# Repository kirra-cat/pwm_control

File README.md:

# pwm_control
Система управления элементами Пельтье

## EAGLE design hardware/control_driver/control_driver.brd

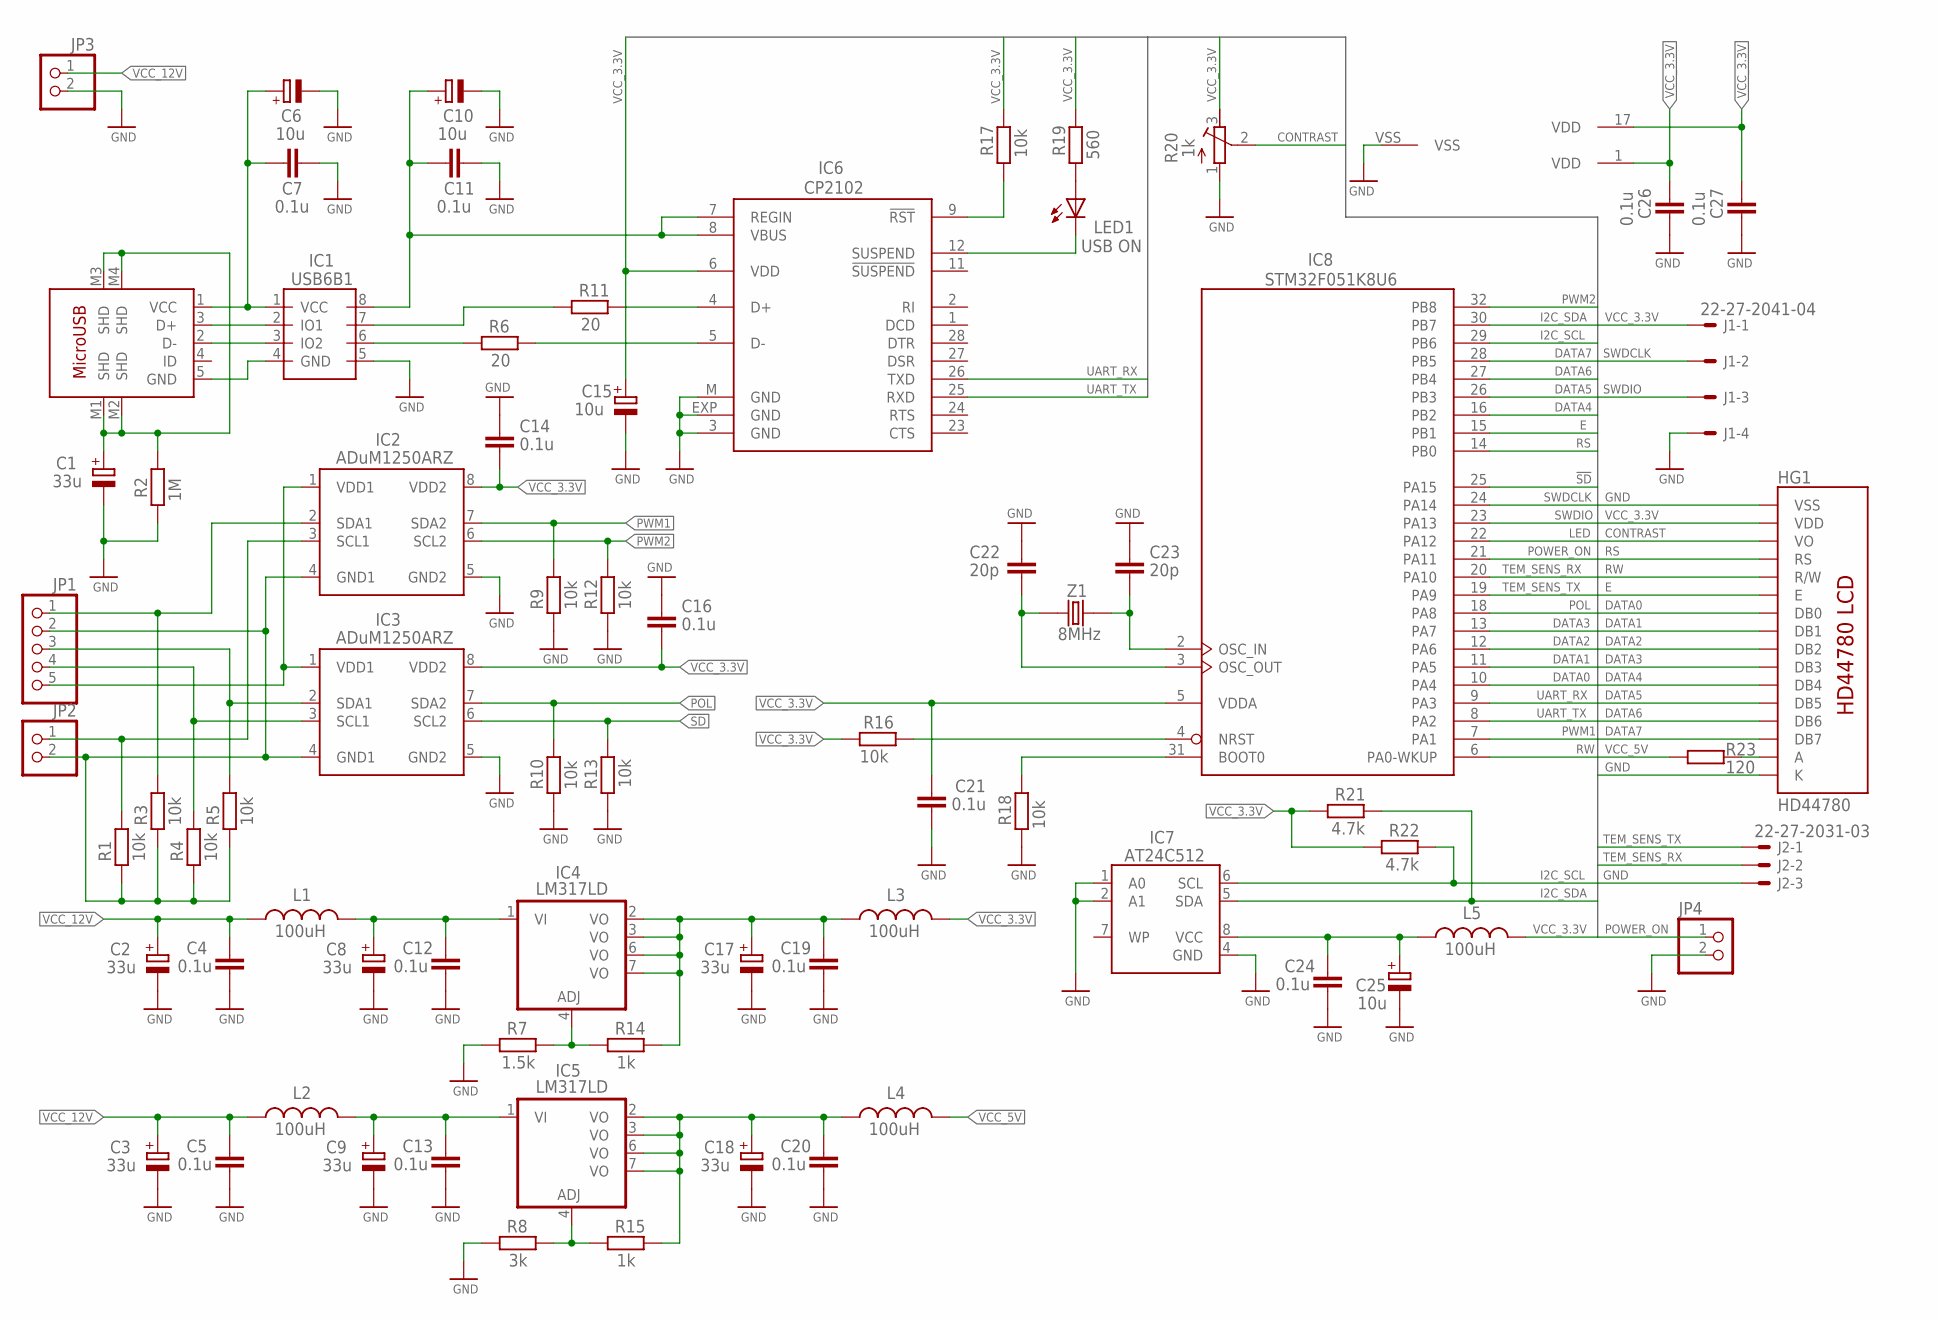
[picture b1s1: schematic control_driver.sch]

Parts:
C1, C17, C18: 33u; SMC_B
C2, C3, C8, C9: 33u; SMC_C
C4, C5, C7, C11, C12, C13, C14, C16, C19, C20, C21, C24, C26, C27: 0.1u; C0603
C6, C10, C15, C25: 10u; SMC_A
C22, C23: 20p; C0603
HG1: HD44780; LCD-16X2-4HOLES
IC1: USB6B1; SO08
IC2, IC3: ADuM1250ARZ; SO8
IC4, IC5: LM317LD; SO08
IC6: CP2102; MLP28
IC7: AT24C512; SO8
IC8: STM32F051K8U6; UFQFPN32
J1: 22-27-2041-04; 6410-04
J2: 22-27-2031-03; 6410-03
JP1: PINHD-1X55X2MM; 1_05X2MM
JP2, JP3, JP4: PINHD-1X2; 1X02
L1, L2, L3, L4, L5: 100uH; C0603
LED1: USB ON; CHIPLED_0805
R1, R3, R4, R5, R9, R10, R12, R13, R16, R17, R18: 10k; R0603
R2: 1M; R0603
R6, R11: 20; R0603
R7: 1.5k; R0603
R8: 3k; R0603
R14, R15: 1k; R0603
R19: 560; R0603
R20: 1k; RTRIM4G/J
R21, R22: 4.7k; R0603
R23: 120; R0805
X1: MICRO-USB; ZX62R-B-5P
Z1: 8MHz; CRYSTAL_5X7

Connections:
!SD: IC3.6 (SCL2), IC8.25 (PA15), R13.2
CONTRAST: HG1.3 (VO), R20.2 (S)
DATA0: HG1.7 (DB0), IC8.10 (PA4)
DATA1: HG1.8 (DB1), IC8.11 (PA5)
DATA2: HG1.9 (DB2), IC8.12 (PA6)
DATA3: HG1.10 (DB3), IC8.13 (PA7)
DATA4: HG1.11 (DB4), IC8.16 (PB2)
DATA5: HG1.12 (DB5), IC8.26 (PB3)
DATA6: HG1.13 (DB6), IC8.27 (PB4)
DATA7: HG1.14 (DB7), IC8.28 (PB5)
E: HG1.6 (E), IC8.15 (PB1)
GND: C1.-, C2.-, C3.-, C4.1, C5.1, C6.-, C7.2, C8.-, C9.-, C10.-, C11.2, C12.1, C13.1, C14.2, C15.-, C16.2, C17.-, C18.-, C19.1, C20.1, C21.1, C22.2, C23.2, C24.1, C25.-, C26.1, C27.1, HG1.1 (VSS), HG1.16 (K), IC1.5 (GND), IC2.5 (GND2), IC3.5 (GND2), IC6.3 (GND), IC6.EXP (GND), IC6.M (GND), IC7.1 (A0), IC7.2 (A1), IC7.4 (GND), IC8.VSS, J1.4, J2.3, JP3.2, JP4.2, R2.1, R7.1, R8.1, R9.1, R10.1, R12.1, R13.1, R18.1, R20.1 (A)
I2C_SCL: IC7.6 (SCL), IC8.29 (PB6), R22.2
I2C_SDA: IC7.5 (SDA), IC8.30 (PB7), R21.2
LED: IC8.22 (PA12)
unnamed: HG1.15 (A), R23.2
unnamed: IC1.6 (IO2), R6.1
unnamed: IC1.7 (IO1), R11.1
unnamed: IC6.5 (D-), R6.2
unnamed: IC6.4 (D+), R11.2
unnamed: LED1.A, R19.1
unnamed: C10.+, C11.1, IC1.8 (VCC), IC6.7 (REGIN), IC6.8 (VBUS)
unnamed: IC6.9 (!RST), R17.1
unnamed: IC6.12 (SUSPEND), LED1.C
unnamed: IC4.4 (ADJ), R7.2, R14.1
unnamed: C8.+, C12.2, IC4.1 (VI), L1.2
unnamed: IC5.4 (ADJ), R8.2, R15.1
unnamed: C1.+, R2.2, X1.M1 (SHD), X1.M2 (SHD), X1.M3 (SHD), X1.M4 (SHD)
unnamed: IC1.2 (IO1), X1.3 (D+)
unnamed: IC1.3 (IO2), X1.2 (D-)
unnamed: IC1.4 (GND), X1.5 (GND)
unnamed: C6.+, C7.1, IC1.1 (VCC), X1.1 (VCC)
unnamed: C22.1, IC8.3 (OSC_OUT), Z1.P$1 (1)
unnamed: C23.1, IC8.2 (OSC_IN), Z1.P$2 (2)
unnamed: C24.2, C25.+, IC7.8 (VCC), L5.1
unnamed: IC8.4 (NRST), R16.2
unnamed: IC2.1 (VDD1), IC3.1 (VDD1), JP1.5
unnamed: IC8.31 (BOOT0), R18.2
unnamed: IC2.3 (SCL1), JP2.1, R1.2
unnamed: IC2.2 (SDA1), JP1.1, R3.2
unnamed: IC3.2 (SDA1), JP1.3, R5.2
unnamed: IC3.3 (SCL1), JP1.4, R4.2
unnamed: IC2.4 (GND1), IC3.4 (GND1), JP1.2, JP2.2, R1.1, R3.1, R4.1, R5.1
POL: IC3.7 (SDA2), IC8.18 (PA8), R10.2
POWER_ON: IC8.21 (PA11), JP4.1
PWM1: IC2.7 (SDA2), IC8.7 (PA1), R9.2
PWM2: IC2.6 (SCL2), IC8.32 (PB8), R12.2
RS: HG1.4 (RS), IC8.14 (PB0)
RW: HG1.5 (R/W), IC8.6 (PA0-WKUP)
SWDCLK: IC8.24 (PA14), J1.2
SWDIO: IC8.23 (PA13), J1.3
TEM_SENS_RX: IC8.20 (PA10), J2.2
TEM_SENS_TX: IC8.19 (PA9), J2.1
UART_RX: IC6.26 (TXD), IC8.9 (PA3)
UART_TX: IC6.25 (RXD), IC8.8 (PA2)
VCC_3.3V: C14.1, C15.+, C16.1, C21.2, C26.2, C27.2, HG1.2 (VDD), IC2.8 (VDD2), IC3.8 (VDD2), IC6.6 (VDD), IC8.1 (VDD), IC8.5 (VDDA), IC8.17 (VDD), J1.1, L3.2, L5.2, R16.1, R17.2, R19.2, R20.3 (E), R21.1, R22.1
VCC_3.3V1: C18.+, C20.2, IC5.2 (VO), IC5.3 (VO), IC5.6 (VO), IC5.7 (VO), L4.1, R15.2
VCC_3.3V2222: C17.+, C19.2, IC4.2 (VO), IC4.3 (VO), IC4.6 (VO), IC4.7 (VO), L3.1, R14.2
VCC_5V: L4.2, R23.1
VCC_12V: C2.+, C3.+, C4.2, C5.2, JP3.1, L1.1, L2.1
VCC_12V_IN: C9.+, C13.2, IC5.1 (VI), L2.2

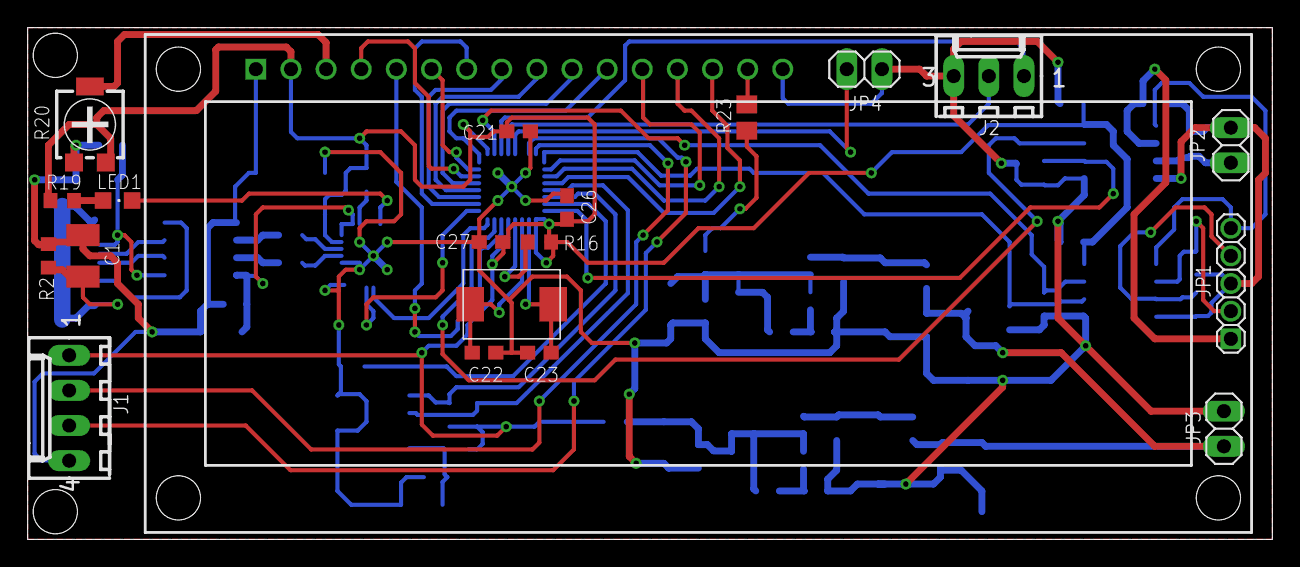
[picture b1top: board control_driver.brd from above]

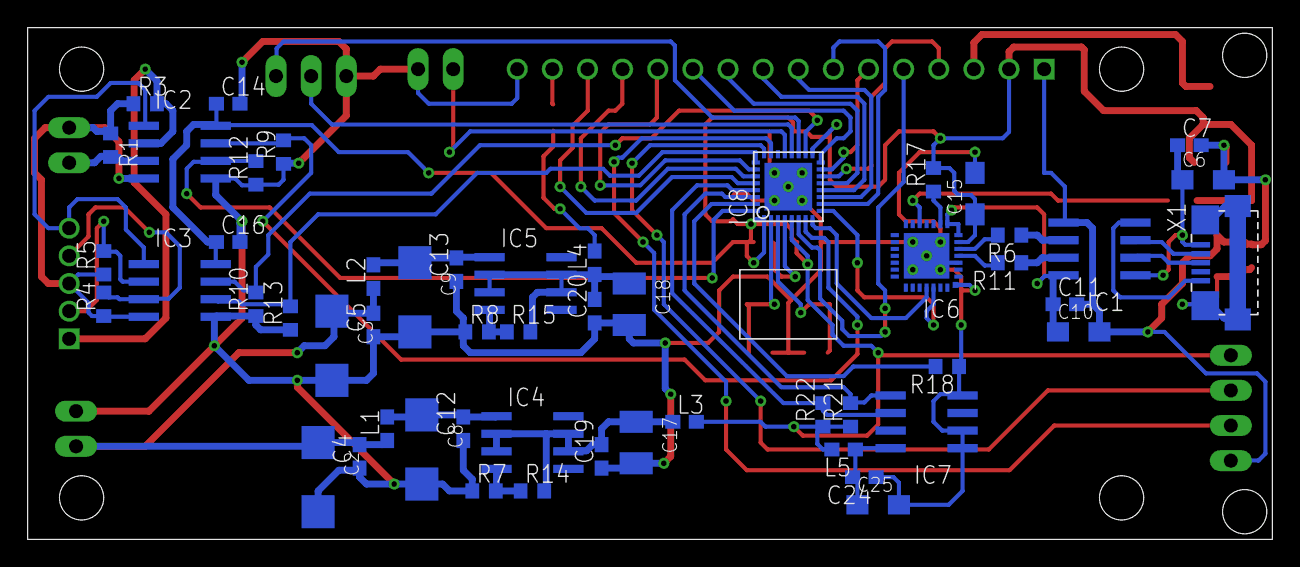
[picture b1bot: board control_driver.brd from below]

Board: 2 copper layers, 89.9 x 36.9 mm, 73 parts (53 on the bottom side), 60 nets.

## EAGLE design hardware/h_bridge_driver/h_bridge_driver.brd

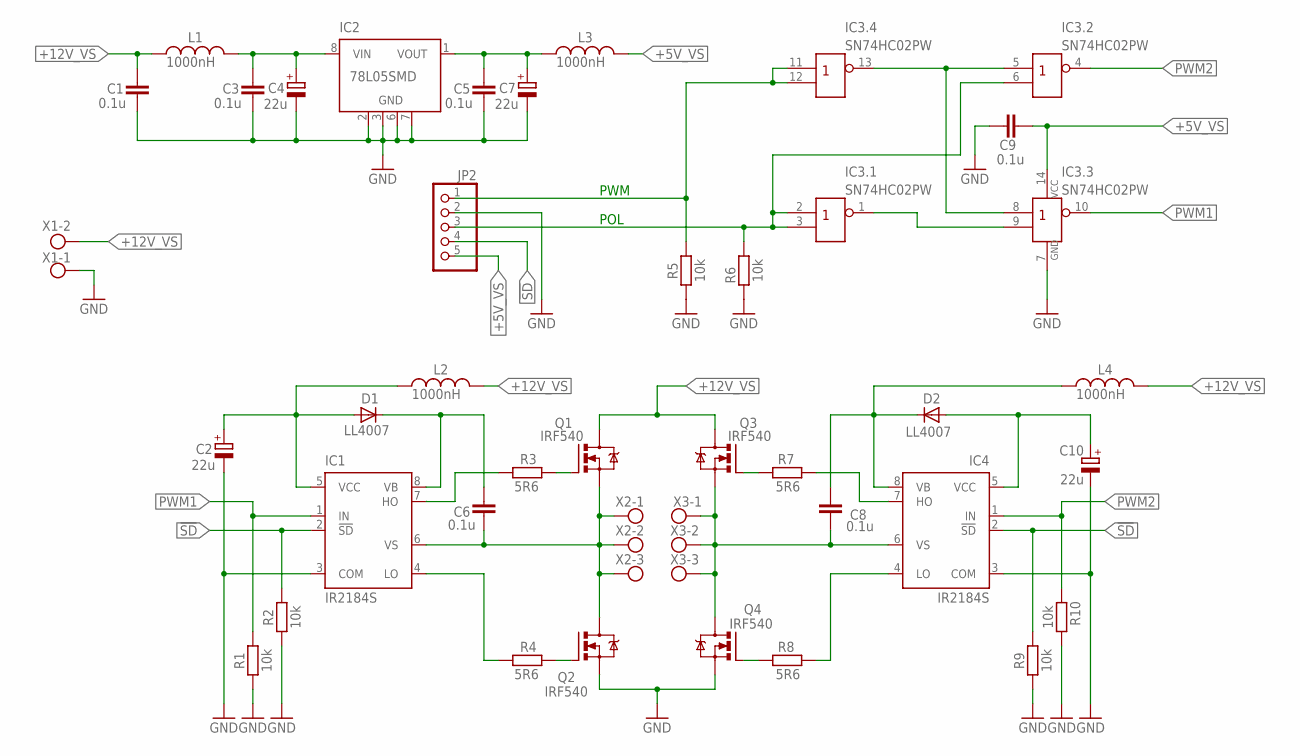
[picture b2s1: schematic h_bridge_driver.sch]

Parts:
C1, C3, C5, C6, C8, C9: 0.1u; C1206
C2, C4, C7, C10: 22u; SMC_C
D1, D2: LL4007; MINIMELF
IC1, IC4: IR2184S; SO08
IC2: 78L05SMD; SO08
IC3: SN74HC02PW; SO14
JP2: PINHD-1X55X2MM; 1_05X2MM
L1, L2, L3, L4: 1000nH; L1812
Q1, Q2, Q3, Q4: IRF540; TO220BV
R1, R2, R5, R6, R9, R10: 10k; R0603
R3, R4, R7, R8: 5R6; R0603
X1: MKDSN1,5/2-5,08
X2, X3: MKDSN1,5/3-5,08

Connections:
!SD: IC1.2 (!SD), IC4.2 (!SD), JP2.4, R2.2, R9.2
+5V_VS: C9.1, IC3.14 (VCC), JP2.5, L3.2
+12V_VS: C1.1, L1.1, L2.2, L4.2, Q1.D, Q3.D, X1.2
GND: C1.2, C2.-, C3.2, C4.-, C5.2, C7.-, C9.2, C10.-, IC1.3 (COM), IC2.2 (GND), IC2.3 (GND), IC2.6 (GND), IC2.7 (GND), IC3.7 (GND), IC4.3 (COM), JP2.2, Q2.S, Q4.S, R1.1, R2.1, R5.1, R6.1, R9.1, R10.1, X1.1
unnamed: IC1.7 (HO), R3.1
unnamed: Q1.G, R3.2
unnamed: IC1.4 (LO), R4.1
unnamed: Q2.G, R4.2
unnamed: C6.1, D1.C, IC1.8 (VB)
unnamed: C6.2, IC1.6 (VS), Q1.S, Q2.D, X2.1, X2.2, X2.3
unnamed: Q3.G, R7.2
unnamed: C2.+, D1.A, IC1.5 (VCC), L2.1
unnamed: IC3.2 (I0), IC3.3 (I1), IC3.6 (I1), JP2.3, R6.2
unnamed: IC3.5 (I0), IC3.8 (I0), IC3.13 (O)
unnamed: IC3.1 (O), IC3.9 (I1)
unnamed: IC3.11 (I0), IC3.12 (I1), JP2.1, R5.2
unnamed: IC4.7 (HO), R7.1
unnamed: Q4.G, R8.2
unnamed: IC4.4 (LO), R8.1
unnamed: C3.1, C4.+, IC2.8 (VIN), L1.2
unnamed: C8.1, D2.C, IC4.8 (VB), L4.1
unnamed: C8.2, IC4.6 (VS), Q3.S, Q4.D, X3.1, X3.2, X3.3
unnamed: C10.+, D2.A, IC4.5 (VCC)
unnamed: C5.1, C7.+, IC2.1 (VOUT), L3.1
PWM1: IC1.1 (IN), IC3.10 (O), R1.2
PWM2: IC3.4 (O), IC4.1 (IN), R10.2

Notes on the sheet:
PWM
POL

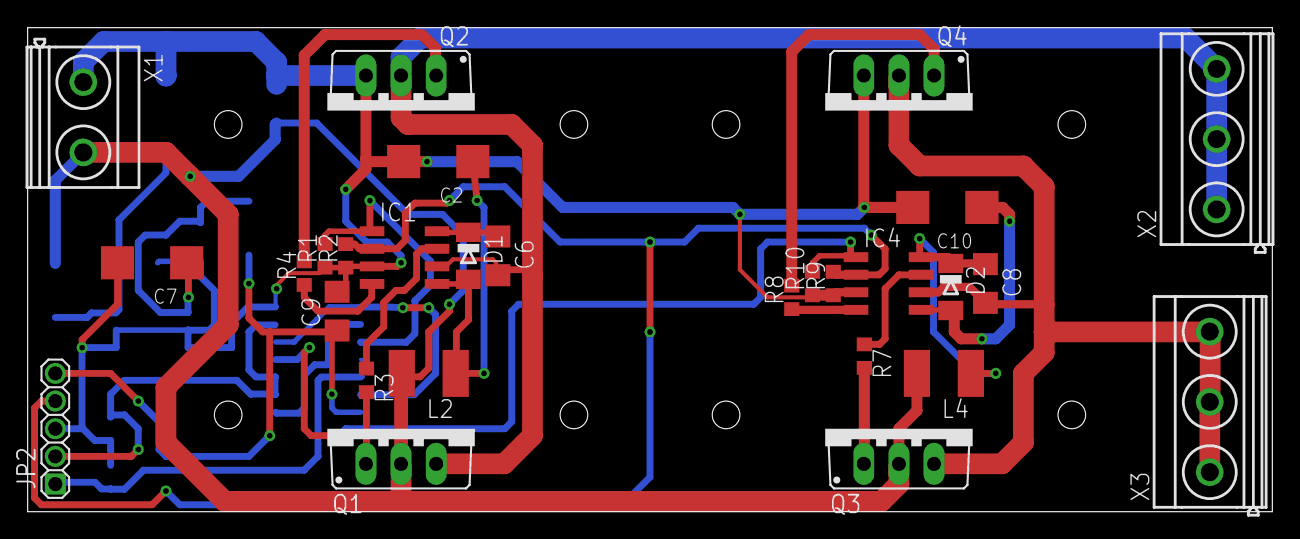
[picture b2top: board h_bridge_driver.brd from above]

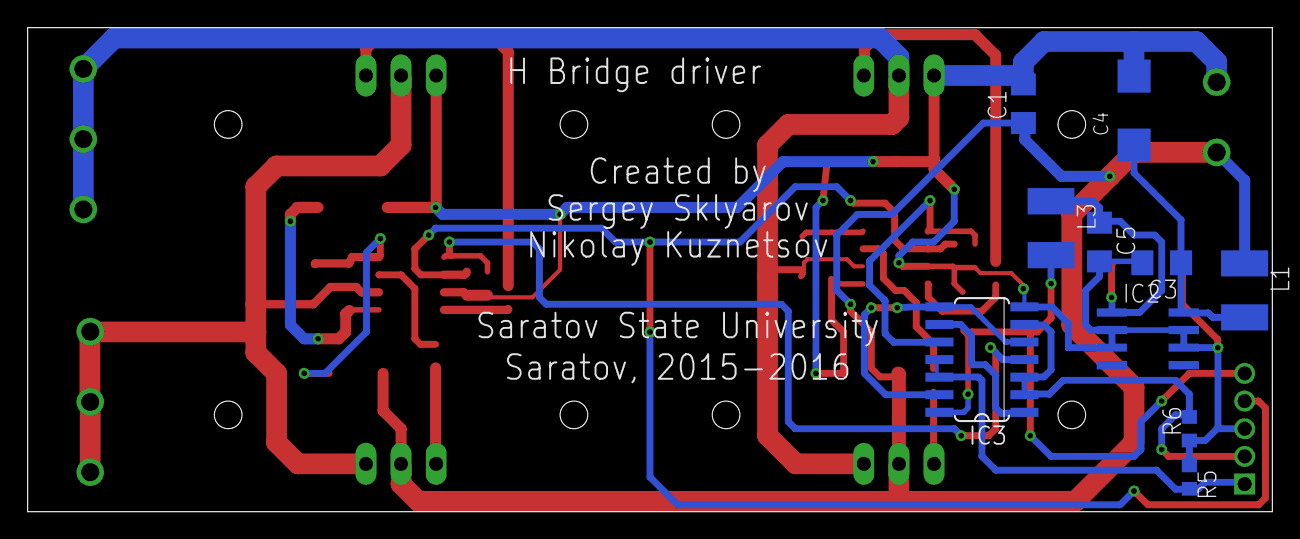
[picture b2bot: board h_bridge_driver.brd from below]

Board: 2 copper layers, 90.0 x 35.0 mm, 42 parts (10 on the bottom side), 26 nets.

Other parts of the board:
U$1, U$2, U$3, U$4: BLA024

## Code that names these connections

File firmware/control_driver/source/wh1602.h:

/*
 * wh1602.h
 *
 *  Created on: 24 мая 2016 г.
 *      Author: kirra
 */

#ifndef WH1602_H_
#define WH1602_H_

#define LCD44780_PIN_RS       GPIO_Pin_0 /** PB0 */
#define LCD44780_PIN_RW       GPIO_Pin_0 /** PA0 */
#define LCD44780_PIN_E        GPIO_Pin_1 /** PB1 */

#define LCD44780_DATA         GPIO_Pin_2 | GPIO_Pin_3 | GPIO_Pin_4 | GPIO_Pin_5 /** PB2-PB5 */
#define LCD44780_DATA_OFFSET  2

void LCD44780_Delay(uint32_t t);

void LCD44780_WriteNibble(uint8_t data);

void LCD44780_WriteByte(uint8_t data);

void LCD44780_GoToLine(uint8_t LineNum);

void LCD44780_ClearDisplay(void);

void LCD44780_SetCursorPosition(uint8_t x, uint8_t y);

void LCD44780_ShowChar(uint8_t c);

void LCD44780_ShowString(uint8_t *s);

void LCD44780_Initialization(void);

#endif /* WH1602_H_ */

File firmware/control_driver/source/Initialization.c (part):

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	GPIO_PinAFConfig(GPIOD, GPIO_PinSource9, GPIO_AF_1);
	GPIO_PinAFConfig(GPIOD, GPIO_PinSource10, GPIO_AF_1);

	/** PA2, PA9 -> TX UART */
	GPIO_InitStructure.GPIO_OType = GPIO_OType_PP;
	GPIO_InitStructure.GPIO_PuPd = GPIO_PuPd_UP;
	GPIO_InitStructure.GPIO_Mode = GPIO_Mode_AF;
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	GPIO_InitStructure.GPIO_Speed = GPIO_Speed_50MHz;
	GPIO_Init(GPIOD, &GPIO_InitStructure);

	/** PA3, PA10  -> RX UART. */
	GPIO_InitStructure.GPIO_Mode = GPIO_Mode_AF;
	GPIO_InitStructure.GPIO_PuPd = GPIO_PuPd_NOPULL;
	GPIO_InitStructure.GPIO_Pin = GPIO_Pin_3 | GPIO_Pin_10;
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
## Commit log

2016-02-20 Inital commit
2016-02-20 Допиливается котроллер управления
2016-02-22 Добавлена трассиворка платы управления
2016-02-24 Исправленые ошибки в трассировке платы управления
2016-05-30 added firmware (which does not work:()
